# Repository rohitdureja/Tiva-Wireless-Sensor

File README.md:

Tiva-Wireless-Sensor
====================

32-channel neural activity wireless frontend

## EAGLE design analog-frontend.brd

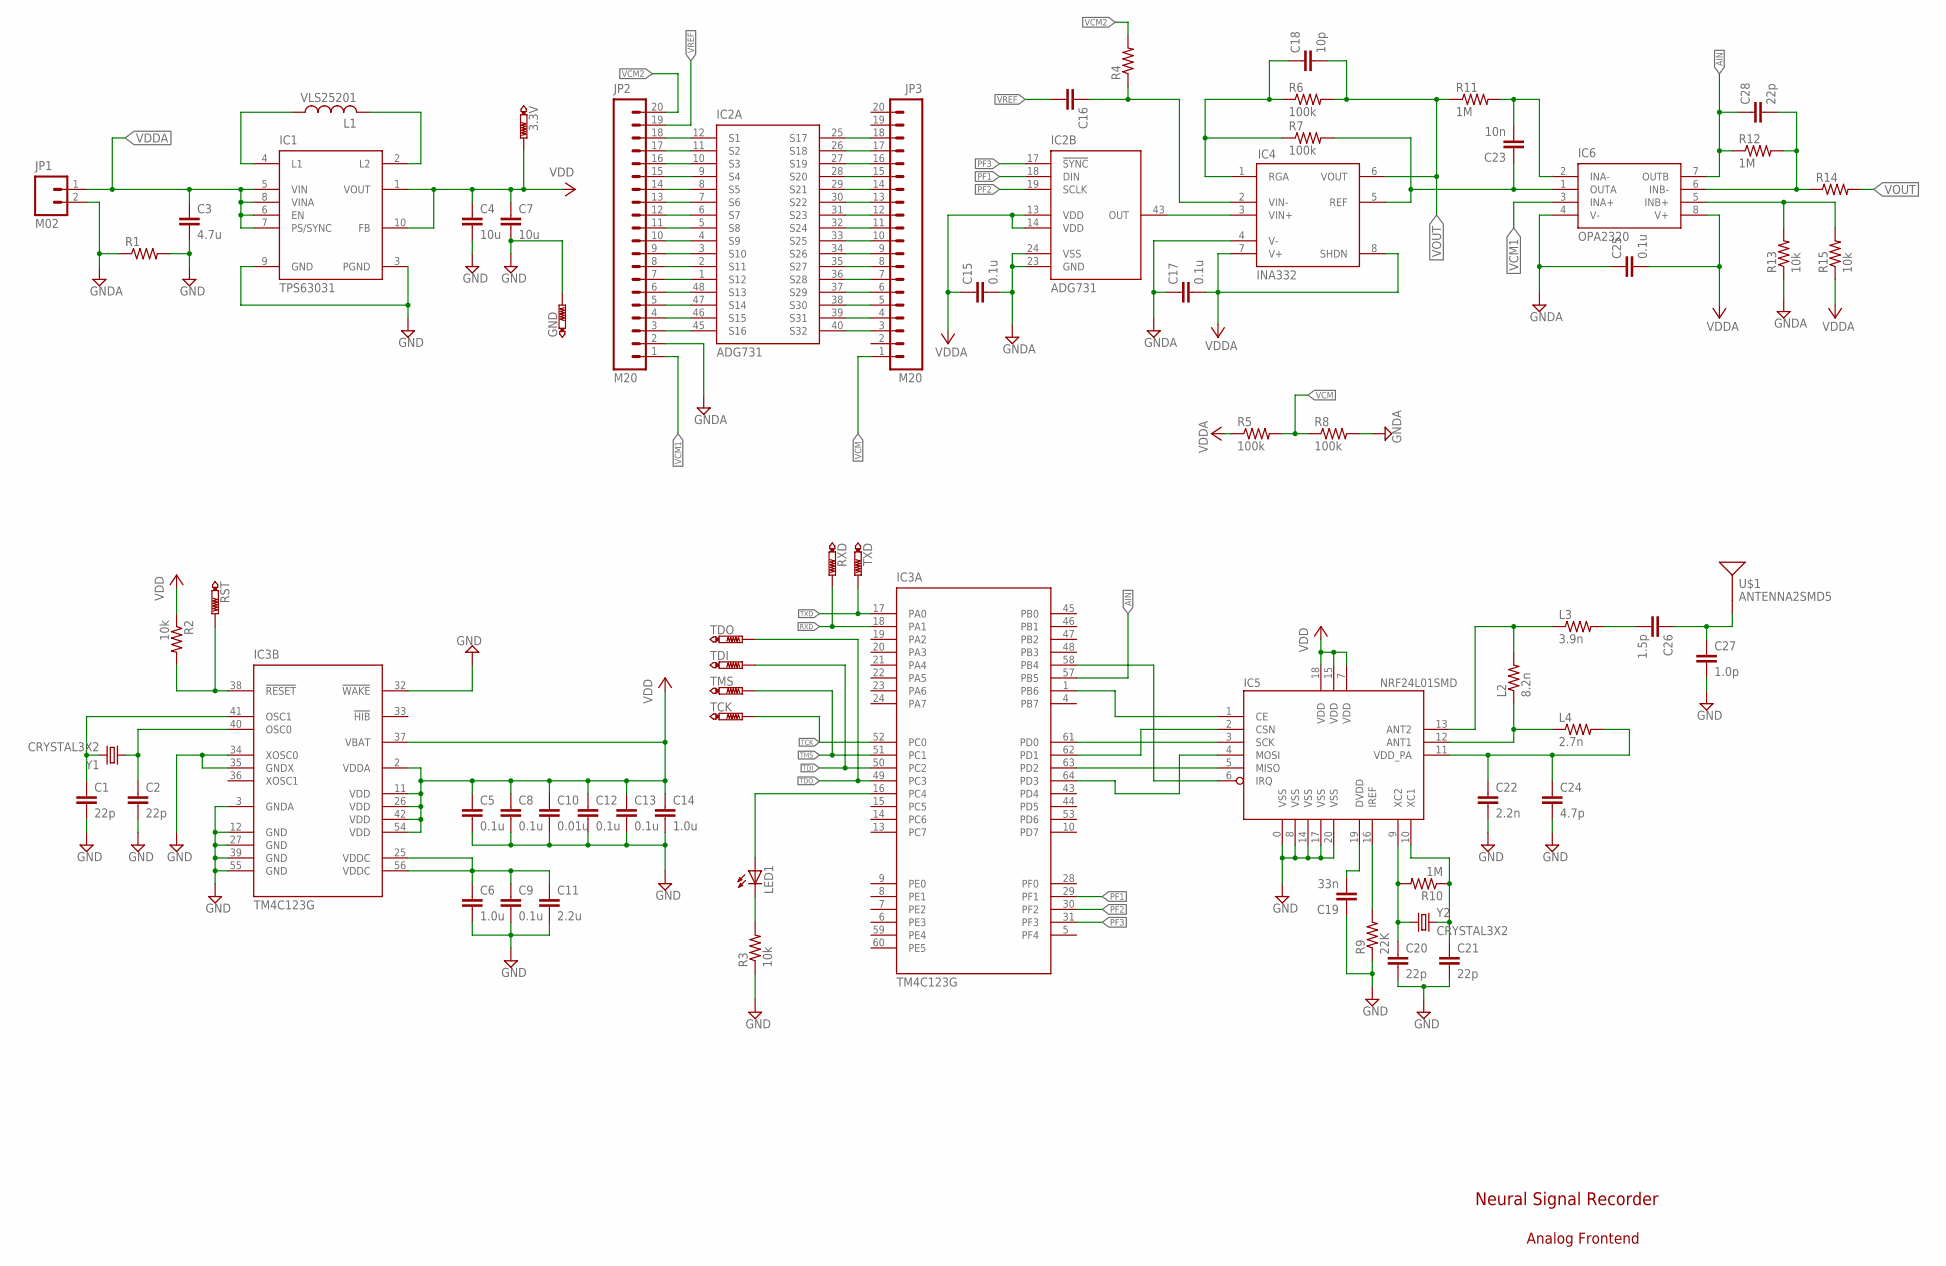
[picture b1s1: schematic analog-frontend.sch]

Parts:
3.3V: PTR1B1,27; B1,27
C1, C2, C20, C21, C28: 22p; C0402
C3: 4.7u; C0402
C4, C7: 10u; C0402
C5, C8, C9, C12, C13, C15, C17, C25: 0.1u; C0402
C6, C14: 1.0u; C0402
C10: 0.01u; C0402
C11: 2.2u; C0402
C16: C-EUC0402; C0402
C18: 10p; C0402
C19: 33n; C0402
C22: 2.2n; C0402
C23: 10n; C0402
C24: 4.7p; C0402
C26: 1.5p; C0402
C27: 1.0p; C0402
GND: PTR1B1,27; B1,27
IC1: TPS63031; S-PDSO-N10
IC2: ADG731; LFCSP48
IC3: TM4C123G; LQFP64
IC4: INA332; DGK_S-PDSO-G8
IC5: NRF24L01SMD; QFN20
IC6: OPA2320; MSOP08
JP1: M02; 1X02
JP2, JP3: M20; 1X20
L1: VLS25201; L1008
L2: 8.2n; R0402
L3: 3.9n; R0402
L4: 2.7n; R0402
LED1: LED0402; 0402
R1: R-US_R0201; R0201
R2, R3, R13, R15: 10k; R0402
R4, R14: R-US_R0402; R0402
R5, R6, R7, R8: 100k; R0402
R9: 22K; R0402
R10, R11, R12: 1M; R0402
RST: PTR1B1,27; B1,27
RXD: PTR1B1,27; B1,27
TCK: PTR1B1,27; B1,27
TDI: PTR1B1,27; B1,27
TDO: PTR1B1,27; B1,27
TMS: PTR1B1,27; B1,27
TXD: PTR1B1,27; B1,27
U$1: ANTENNA2SMD5; ANTENNA-CHIP5
Y1, Y2: CRYSTAL3X2; SMDCRYSTAL3X2

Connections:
+3V3: 3.3V.TP, C4.1, C5.1, C7.1, C8.1, C10.1, C12.1, C13.1, C14.1, IC1.1 (VOUT), IC1.10 (FB), IC3.2 (VDDA), IC3.11 (VDD), IC3.26 (VDD), IC3.37 (VBAT), IC3.42 (VDD), IC3.54 (VDD), IC5.7 (VDD), IC5.15 (VDD), IC5.18 (VDD), R2.1
AIN: C28.1, IC3.57 (PB5), IC6.7 (OUTB), R12.1
GND: C1.2, C2.2, C3.2, C4.2, C5.2, C6.2, C7.2, C8.2, C9.2, C10.2, C11.2, C12.2, C13.2, C14.2, C19.1, C20.2, C21.2, C22.2, C24.2, C27.2, GND.TP, IC1.3 (PGND), IC1.9 (GND), IC3.3 (GNDA), IC3.12 (GND), IC3.27 (GND), IC3.32 (!WAKE!), IC3.34 (XOSC0), IC3.35 (GNDX), IC3.39 (GND), IC3.55 (GND), IC5.0 (VSS), IC5.8 (VSS), IC5.14 (VSS), IC5.17 (VSS), IC5.20 (VSS), R1.2, R3.1, R9.1
GNDA: C15.2, C17.1, C25.1, IC2.23 (GND), IC2.24 (VSS), IC4.4 (V-), IC6.4 (V-), JP1.2, JP2.2, R1.1, R8.2, R13.1
unnamed: IC2.12 (S1), JP2.18
unnamed: IC2.45 (S16), JP2.3
unnamed: IC2.25 (S17), JP3.18
unnamed: IC2.40 (S32), JP3.3
unnamed: IC2.11 (S2), JP2.17
unnamed: IC2.10 (S3), JP2.16
unnamed: IC2.9 (S4), JP2.15
unnamed: IC2.8 (S5), JP2.14
unnamed: IC2.7 (S6), JP2.13
unnamed: IC2.6 (S7), JP2.12
unnamed: IC2.5 (S8), JP2.11
unnamed: IC2.4 (S9), JP2.10
unnamed: IC2.3 (S10), JP2.9
unnamed: IC2.2 (S11), JP2.8
unnamed: IC2.1 (S12), JP2.7
unnamed: IC2.48 (S13), JP2.6
unnamed: IC2.47 (S14), JP2.5
unnamed: IC2.46 (S15), JP2.4
unnamed: IC2.26 (S18), JP3.17
unnamed: IC2.27 (S19), JP3.16
unnamed: IC2.28 (S20), JP3.15
unnamed: IC2.29 (S21), JP3.14
unnamed: IC2.30 (S22), JP3.13
unnamed: IC2.31 (S23), JP3.12
unnamed: IC2.32 (S24), JP3.11
unnamed: IC2.33 (S25), JP3.10
unnamed: IC2.34 (S26), JP3.9
unnamed: IC2.35 (S27), JP3.8
unnamed: IC2.36 (S28), JP3.7
unnamed: IC2.37 (S29), JP3.6
unnamed: IC2.38 (S30), JP3.5
unnamed: IC2.39 (S31), JP3.4
unnamed: IC1.4 (L1), L1.P$1 (1)
unnamed: IC1.2 (L2), L1.P$2 (2)
unnamed: IC2.43 (OUT), IC4.3 (VIN+)
unnamed: C23.1, IC4.5 (REF), IC6.1 (OUTA), R7.2
unnamed: C2.1, IC3.40 (OSC0), Y1.1
unnamed: C18.1, IC4.1 (RGA), R6.1, R7.1
unnamed: C28.2, IC6.6 (INB-), R12.2, R14.1
unnamed: C1.1, IC3.41 (OSC1), Y1.3 (2)
unnamed: C23.2, IC6.2 (INA-), R11.2
unnamed: C19.2, IC5.19 (DVDD)
unnamed: IC5.16 (IREF), R9.2
unnamed: C6.1, C9.1, C11.1, IC3.25 (VDDC), IC3.56 (VDDC)
unnamed: C20.1, IC5.9 (XC2), R10.2, Y2.1
unnamed: IC6.5 (INB+), R13.2, R15.2
unnamed: C21.1, IC5.10 (XC1), R10.1, Y2.3 (2)
unnamed: IC3.38 (!RESET!), R2.2, RST.TP
unnamed: IC5.12 (ANT1), L2.1, L4.1
unnamed: IC5.13 (ANT2), L2.2, L3.1
unnamed: C22.1, C24.1, IC5.11 (VDD_PA), L4.2
unnamed: C26.2, L3.2
unnamed: C26.1, C27.1, U$1.FEED
unnamed: IC3.61 (PD0), IC5.3 (SCK)
unnamed: IC3.62 (PD1), IC5.2 (CSN)
unnamed: IC3.63 (PD2), IC5.5 (MISO)
unnamed: IC3.1 (PB6), IC5.1 (CE)
unnamed: IC3.58 (PB4), IC5.6 (IRQ)
unnamed: IC3.64 (PD3), IC5.4 (MOSI)
unnamed: C16.1, IC4.2 (VIN-), R4.1
unnamed: IC3.16 (PC4), LED1.1 (A)
unnamed: LED1.2 (C), R3.2
PF1: IC2.18 (DIN), IC3.29 (PF1)
PF2: IC2.19 (SCLK), IC3.30 (PF2)
PF3: IC2.17 (!SYNC!), IC3.31 (PF3)
RXD: IC3.18 (PA1), RXD.TP
TCK: IC3.52 (PC0), TCK.TP
TDI: IC3.50 (PC2), TDI.TP
TDO: IC3.49 (PC3), TDO.TP
TMS: IC3.51 (PC1), TMS.TP
TXD: IC3.17 (PA0), TXD.TP
VCM: JP3.1, R5.2, R8.1
VCM1: IC6.3 (INA+), JP2.1
VCM2: JP2.20, R4.2
VDDA: C3.1, C15.1, C17.2, C25.2, IC1.5 (VIN), IC1.6 (EN), IC1.7 (PS/SYNC), IC1.8 (VINA), IC2.13 (VDD), IC2.14 (VDD), IC4.7 (V+), IC4.8 (SHDN), IC6.8 (V+), JP1.1, R5.1, R15.1
VOUT: C18.2, IC4.6 (VOUT), R6.2, R11.1, R14.2
VREF: C16.2, JP2.19

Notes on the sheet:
Neural Signal Recorder
Analog Frontend

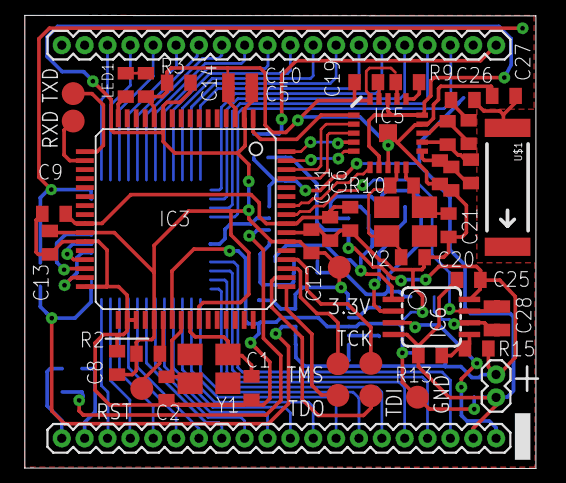
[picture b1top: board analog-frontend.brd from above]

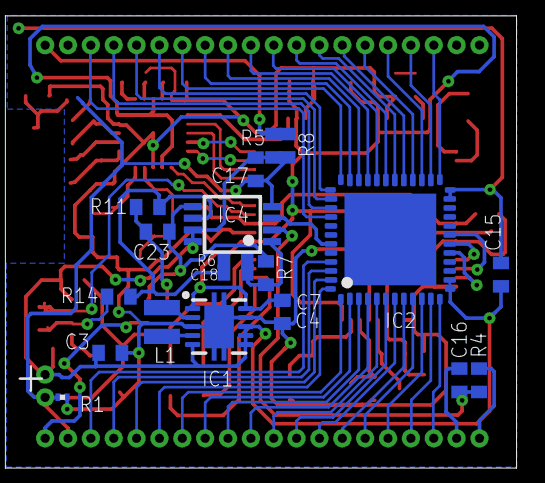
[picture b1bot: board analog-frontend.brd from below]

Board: 2 copper layers, 69 parts (20 on the bottom side), 81 nets.

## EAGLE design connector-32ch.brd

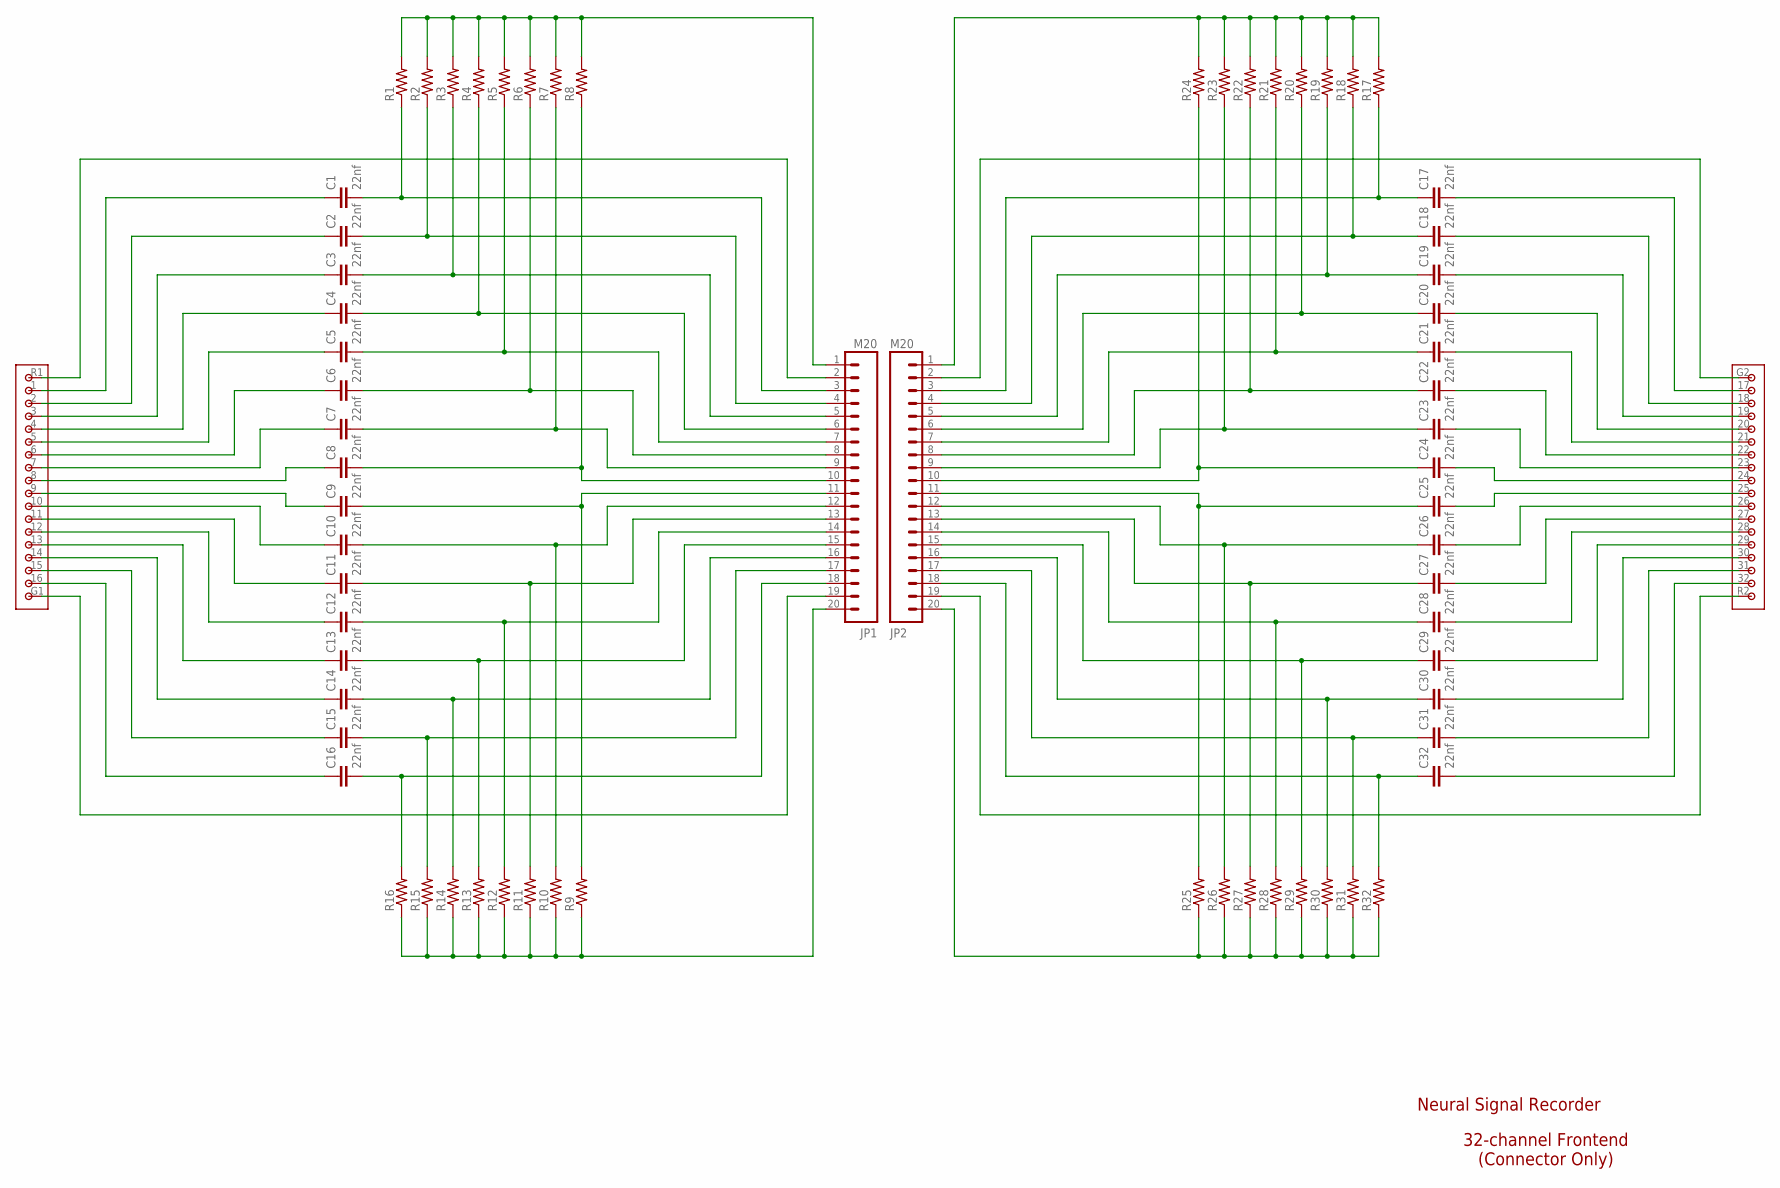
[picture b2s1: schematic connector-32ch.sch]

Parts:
C1, C2, C3, C4, C5, C6, C7, C8, C9, C10, C11, C12, C13, C14, C15, C16, C17, C18, C19, C20, C21, C22, C23, C24, C25, C26, C27, C28, C29, C30, C31, C32: 22nf; C0402
JP1, JP2: M20; 1X20
R1, R2, R3, R4, R5, R6, R7, R8, R9, R10, R11, R12, R13, R14, R15, R16, R17, R18, R19, R20, R21, R22, R23, R24, R25, R26, R27, R28, R29, R30, R31, R32: R-US_R0402; R0402
X1: OMNETICS_36PAD; OMNETICS36PADSMT

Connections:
G: JP1.2, JP2.19, X1.R1, X1.R2
unnamed: C8.1, X1.8
unnamed: C9.1, X1.9
unnamed: C7.1, X1.7
unnamed: C6.1, X1.6
unnamed: C5.1, X1.5
unnamed: C4.1, X1.4
unnamed: C3.1, X1.3
unnamed: C2.1, X1.2
unnamed: C1.1, X1.1
unnamed: C10.1, X1.10
unnamed: C11.1, X1.11
unnamed: C12.1, X1.12
unnamed: C13.1, X1.13
unnamed: C14.1, X1.14
unnamed: C15.1, X1.15
unnamed: C16.1, X1.16
unnamed: C24.2, X1.24
unnamed: C25.2, X1.25
unnamed: C23.2, X1.23
unnamed: C22.2, X1.22
unnamed: C21.2, X1.21
unnamed: C20.2, X1.20
unnamed: C19.2, X1.19
unnamed: C18.2, X1.18
unnamed: C17.2, X1.17
unnamed: C26.2, X1.26
unnamed: C27.2, X1.27
unnamed: C28.2, X1.28
unnamed: C29.2, X1.29
unnamed: C30.2, X1.30
unnamed: C31.2, X1.31
unnamed: C32.2, X1.32
unnamed: C1.2, JP1.3, R1.1
unnamed: C2.2, JP1.4, R2.1
unnamed: C3.2, JP1.5, R3.1
unnamed: C4.2, JP1.6, R4.1
unnamed: C5.2, JP1.7, R5.1
unnamed: C6.2, JP1.8, R6.1
unnamed: C7.2, JP1.9, R7.1
unnamed: C8.2, JP1.10, R8.1
unnamed: C9.2, JP1.11, R9.2
unnamed: C10.2, JP1.12, R10.2
unnamed: C11.2, JP1.13, R11.2
unnamed: C12.2, JP1.14, R12.2
unnamed: C13.2, JP1.15, R13.2
unnamed: C14.2, JP1.16, R14.2
unnamed: C15.2, JP1.17, R15.2
unnamed: C16.2, JP1.18, R16.2
unnamed: C17.1, JP2.3, R17.1
unnamed: C18.1, JP2.4, R18.1
unnamed: C19.1, JP2.5, R19.1
unnamed: C20.1, JP2.6, R20.1
unnamed: C21.1, JP2.7, R21.1
unnamed: C22.1, JP2.8, R22.1
unnamed: C23.1, JP2.9, R23.1
unnamed: C24.1, JP2.10, R24.1
unnamed: C25.1, JP2.11, R25.2
unnamed: C26.1, JP2.12, R26.2
unnamed: C27.1, JP2.13, R27.2
unnamed: C28.1, JP2.14, R28.2
unnamed: C29.1, JP2.15, R29.2
unnamed: C30.1, JP2.16, R30.2
unnamed: C31.1, JP2.17, R31.2
unnamed: C32.1, JP2.18, R32.2
R: JP1.19, JP2.2, X1.G1, X1.G2
VCM: JP1.1, JP1.20, JP2.1, JP2.20, R1.2, R2.2, R3.2, R4.2, R5.2, R6.2, R7.2, R8.2, R9.1, R10.1, R11.1, R12.1, R13.1, R14.1, R15.1, R16.1, R17.2, R18.2, R19.2, R20.2, R21.2, R22.2, R23.2, R24.2, R25.1, R26.1, R27.1, R28.1, R29.1, R30.1, R31.1, R32.1

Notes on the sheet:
Neural Signal Recorder
32-channel Frontend (Connector Only)

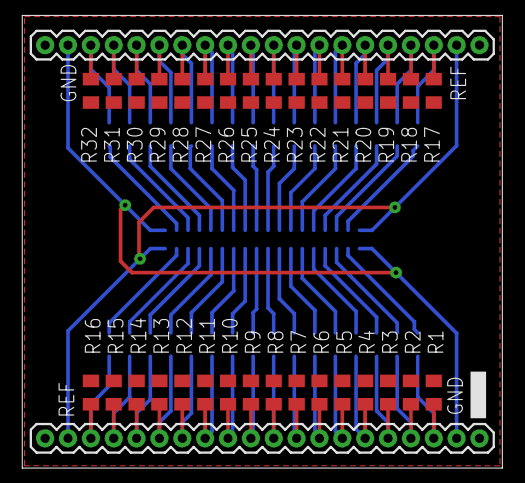
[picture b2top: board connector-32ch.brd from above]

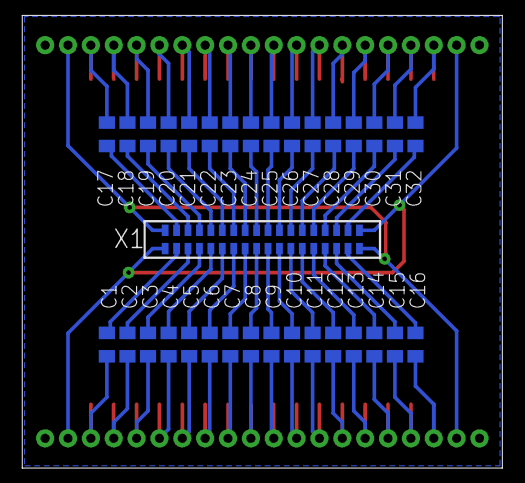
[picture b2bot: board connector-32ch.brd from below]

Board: 2 copper layers, 67 parts (33 on the bottom side), 67 nets.

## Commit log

2014-06-26 created repository
2014-06-27 created neural connector board. G, ref left.
2014-06-27 finished neural connector board.
2014-06-27 edited neural connector. fixed signal plane
2014-06-27 started analog frontend. added mating connectors
2014-06-27 added analog mux
2014-06-29 added power supply circuit
2014-06-30 added mcu, radio and finished analog frontend
2014-07-01 routing complete!
2014-07-01 added signal planes
2014-07-02 fixed analog input connection
2014-07-02 Revert "fixed analog input connection"
    This reverts commit 9ace190f50edbfe5c6ebec0060ae9832deedc051.
2014-07-02 changed all components to 0402
2014-07-03 almost final board files
2014-07-03 changed 32-ch connector size
2014-07-07 minor changes
2014-07-07 minor changes - gerber files
2014-07-07 gerber files
2014-07-07 final files send for fab.
2014-07-07 removed unnecessary files
2014-07-08 fixed commit issue
2014-07-30 added component values
2014-08-01 fixed component values

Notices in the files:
parts and their libraries:
SparkFun-RF: Licensing: Creative Commons ShareAlike 4.0 International - https://creativecommons.org/licenses/by-sa/4.0
